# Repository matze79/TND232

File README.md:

📢 Project: TND232 – RS232 & USB SN76489 Tandy Sound Card

Home Project Site: https://www.retroianer.de

TND232 is a retro-computing hardware and software project to bring authentic Tandy/PCjr style 3-voice sound to IBM-PC compatible computers using modern interfaces like RS232 (serial) and USB, driven by the classic Texas Instruments SN76489 programmable sound generator chip.

🎯 Overview

Many classic DOS games support the Tandy 1000’s 3-voice audio produced by the SN76489 sound chip, but modern vintage add-ons like ISA boards aren’t always practical for newer PCs or laptops without expansion slots. The TND232 project provides an interface to control an SN76489 sound generator externally:

Serial (RS232) interface – connect via the PC’s COM port

USB interface – USB-powered control for systems without RS232

Drives an SN76489 sound module (3 square waves + noise) for authentic sound output on classic software

Includes DOS drivers/utilities to support music and game sound

The goal is to offer a flexible, cross-platform way to add real retro sound hardware to DOS machines without needing an ISA expansion card, while preserving authentic Tandy audio for games and demos.

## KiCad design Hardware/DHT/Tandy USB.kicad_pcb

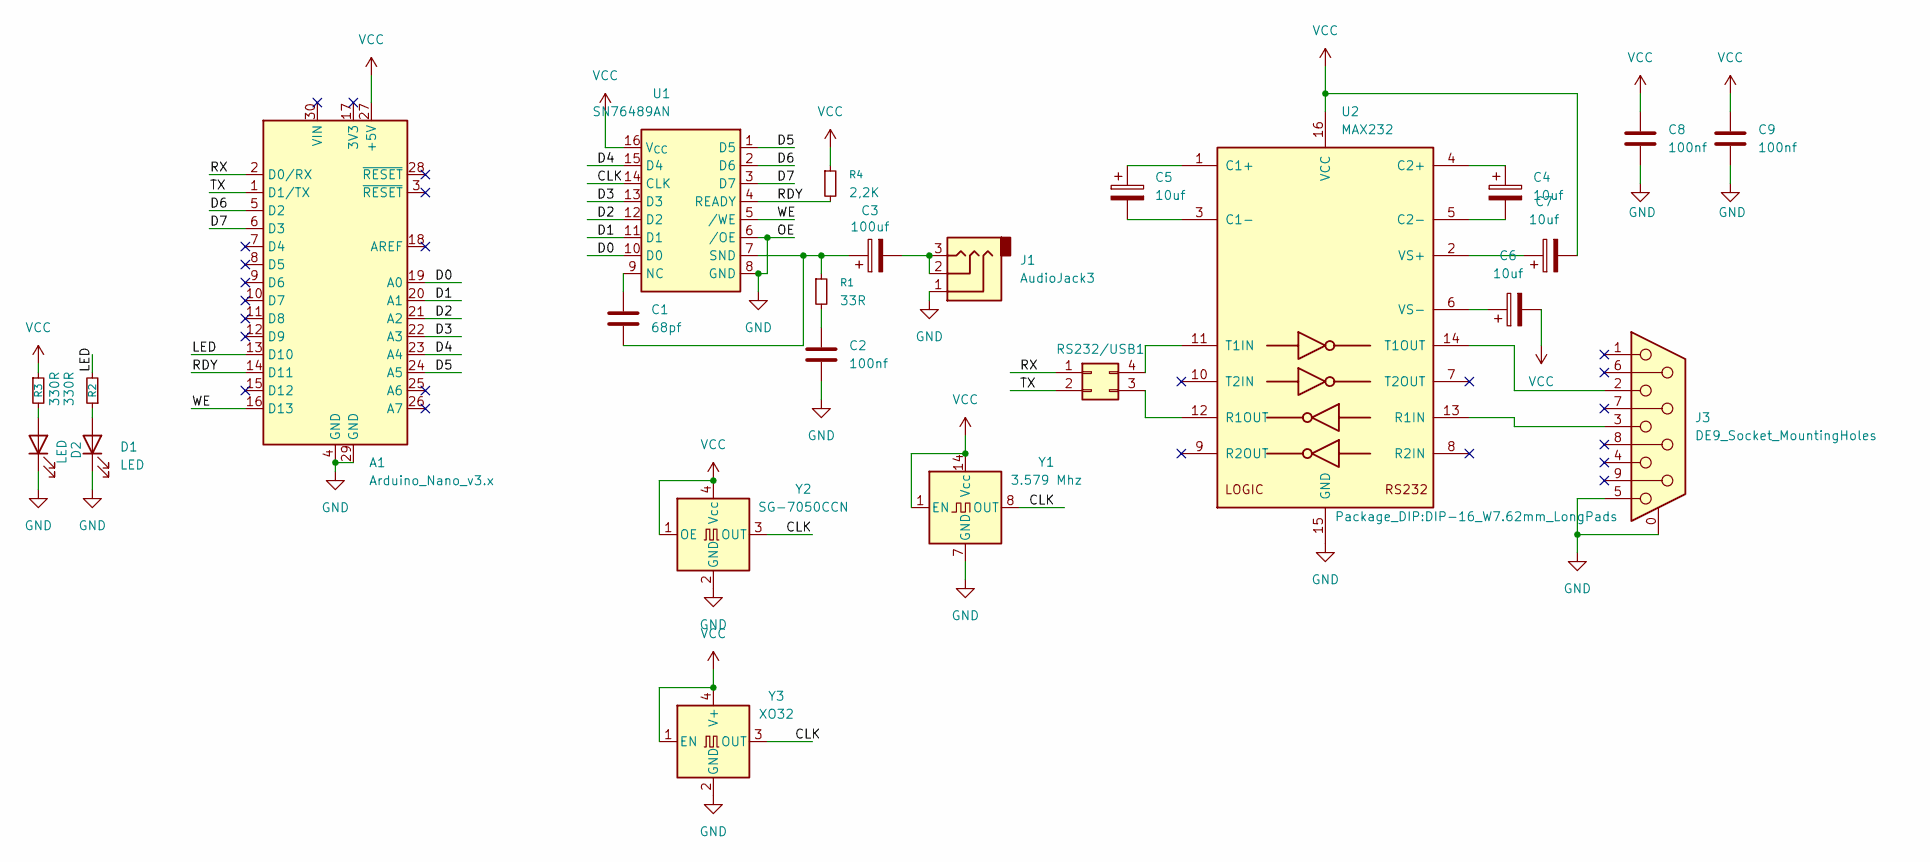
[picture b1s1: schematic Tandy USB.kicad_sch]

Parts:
A1: Arduino_Nano_v3.x; Arduino_Nano
C1: 68pf; C_Disc_D3.4mm_W2.1mm_P2.50mm
C2, C8, C9: 100nf; C_Disc_D3.4mm_W2.1mm_P2.50mm
C3: 100uf; CP_Radial_D5.0mm_P2.50mm
C4, C5, C6, C7: 10uf; CP_Radial_D5.0mm_P2.50mm
D1, D2: LED; LED_D3.0mm
J1: AudioJack3; jack_3.5_pj313d-smt
J3: DE9_Socket_MountingHoles; DSUB-9_Socket_Horizontal_P2.77x2.84mm_EdgePinOffset4.94mm_H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
R1: 33R; R_Axial_DIN0207_L6.3mm_D2.5mm_P10.16mm_Horizontal
R2, R3: 330R; R_Axial_DIN0207_L6.3mm_D2.5mm_P10.16mm_Horizontal
R4: 2,2K; R_Axial_DIN0207_L6.3mm_D2.5mm_P10.16mm_Horizontal
RS232/USB1: Conn_02x02_Counter_Clockwise; PinHeader_2x02_P2.54mm_Vertical
U1: SN76489AN; DIP-16_W7.62mm
U2: MAX232; DIP-16_W7.62mm_LongPads
Y1: 3.579 Mhz; Oscillator_DIP-14
Y2: SG-7050CCN; Oscillator_SMD_SeikoEpson_SG8002CA-4Pin_7.0x5.0mm
Y3: XO32; Oscillator_SMD_EuroQuartz_XO32-4Pin_3.2x2.5mm

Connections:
/CLK: U1.14 (CLK), Y1.8 (OUT), Y2.3 (OUT), Y3.3 (OUT)
/D0: A1.19 (A0), U1.10 (D0)
/D1: A1.20 (A1), U1.11 (D1)
/D2: A1.21 (A2), U1.12 (D2)
/D3: A1.22 (A3), U1.13 (D3)
/D4: A1.23 (A4), U1.15 (D4)
/D5: A1.24 (A5), U1.1 (D5)
/D6: A1.5 (D2), U1.2 (D6)
/D7: A1.6 (D3), U1.3 (D7)
/LED: A1.13 (D10), R2.2
/RDY: A1.14 (D11), R4.2, U1.4 (READY)
/RX: A1.2 (D0/RX), RS232/USB1.1
/TX: A1.1 (D1/TX), RS232/USB1.2
/WE: A1.16 (D13), U1.5 (/WE)
GND: A1.4 (GND), A1.29 (GND), C2.1, C8.1, C9.1, D1.1 (K), D2.1 (K), J1.1, J3.0 (PAD), J3.5, U1.6 (/OE), U1.8 (GND), U2.15 (GND), Y1.7 (GND), Y2.2 (GND), Y3.2 (GND)
unnamed: C2.2, R1.2
unnamed: C3.2, J1.2, J1.3
unnamed: D1.2 (A), R2.1
unnamed: D2.2 (A), R3.2
unnamed: RS232/USB1.3, U2.12 (R1OUT)
unnamed: RS232/USB1.4, U2.11 (T1IN)
unnamed: C1.2, U1.9 (NC)
unnamed: C1.1, C3.1, R1.1, U1.7 (SND)
unnamed: C5.1, U2.1 (C1+)
unnamed: C5.2, U2.3 (C1-)
unnamed: C4.1, U2.4 (C2+)
unnamed: C4.2, U2.5 (C2-)
unnamed: J3.3, U2.13 (R1IN)
unnamed: J3.2, U2.14 (T1OUT)
unnamed: C7.1, U2.2 (VS+)
unnamed: C6.1, U2.6 (VS-)
VCC: A1.27 (+5V), C6.2, C7.2, C8.2, C9.2, R3.1, R4.1, U1.16 (V_{CC}), U2.16 (VCC), Y1.1 (EN), Y1.14 (Vcc), Y2.1 (OE), Y2.4 (Vcc), Y3.1 (EN), Y3.4 (V+)

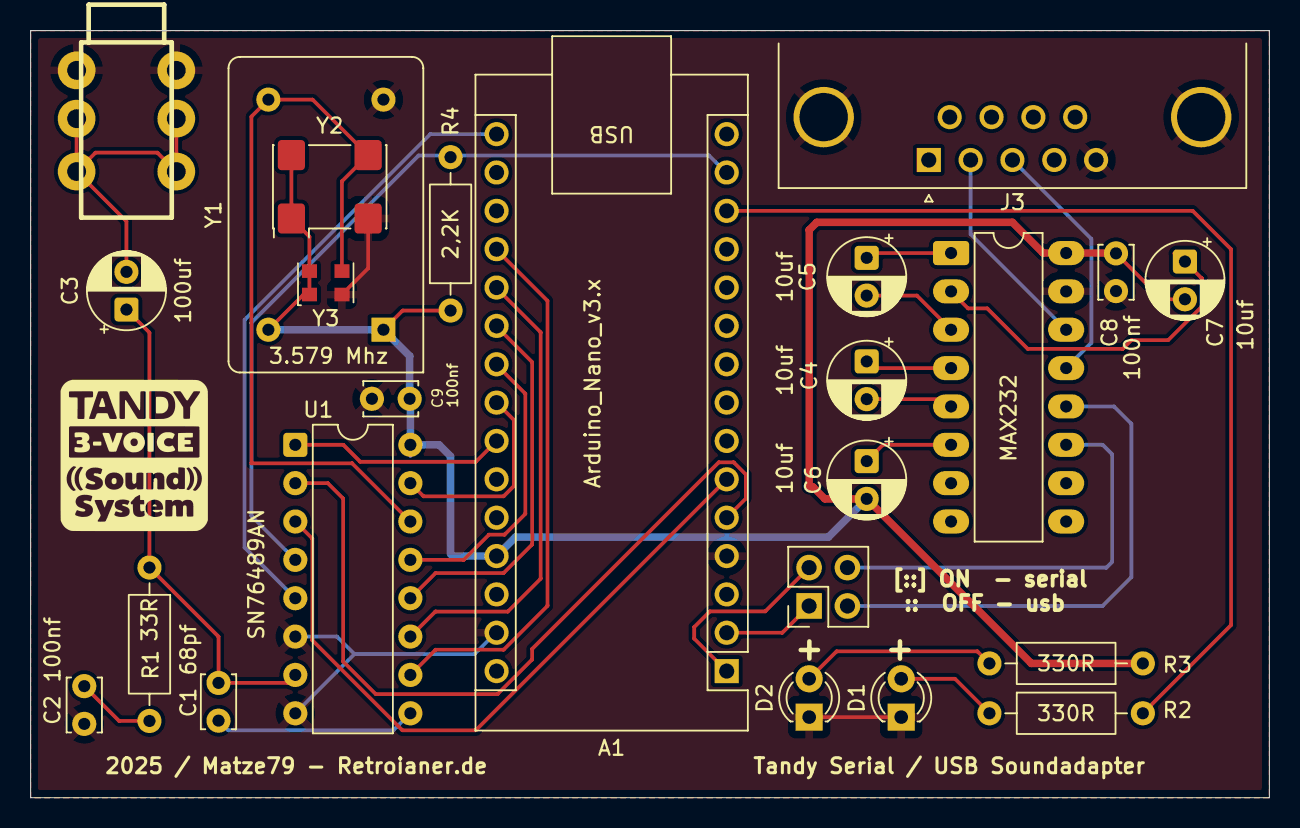
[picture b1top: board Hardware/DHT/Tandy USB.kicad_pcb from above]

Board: 2 copper layers, 82.0 x 50.8 mm, 24 parts (0 on the bottom side), 32 nets.

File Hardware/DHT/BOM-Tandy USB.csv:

Comment,Designator,Footprint,LCSC,Quantity
"2,2K",R4,R_Axial_DIN0207_L6.3mm_D2.5mm_P10.16mm_Horizontal,,1
XO32,Y3,Oscillator_SMD_EuroQuartz_XO32-4Pin_3.2x2.5mm,,1
SG-7050CCN,Y2,Oscillator_SMD_SeikoEpson_SG8002CA-4Pin_7.0x5.0mm,,1
DE9_Socket_MountingHoles,J3,DSUB-9_Socket_Horizontal_P2.77x2.84mm_EdgePinOffset4.94mm_Housed_MountingHolesOffset4.94mm,,1
LED,D1,LED_D3.0mm,,1
LED,D2,LED_D3.0mm,,1
100nf,C9,C_Disc_D3.4mm_W2.1mm_P2.50mm,,1
10uf,C6,CP_Radial_D5.0mm_P2.50mm,,1
100nf,C8,C_Disc_D3.4mm_W2.1mm_P2.50mm,,1
10uf,C7,CP_Radial_D5.0mm_P2.50mm,,1
100nf,C2,C_Disc_D3.4mm_W2.1mm_P2.50mm,,1
SN76489AN,U1,DIP-16_W7.62mm,,1
10uf,C5,CP_Radial_D5.0mm_P2.50mm,,1
3.579 Mhz,Y1,Oscillator_DIP-14,,1
10uf,C4,CP_Radial_D5.0mm_P2.50mm,,1
33R,R1,R_Axial_DIN0207_L6.3mm_D2.5mm_P10.16mm_Horizontal,,1
100uf,C3,CP_Radial_D5.0mm_P2.50mm,,1
68pf,C1,C_Disc_D3.4mm_W2.1mm_P2.50mm,,1
AudioJack3,J1,jack_3.5_pj313d-smt,,1
330R,R2,R_Axial_DIN0207_L6.3mm_D2.5mm_P10.16mm_Horizontal,,1
330R,R3,R_Axial_DIN0207_L6.3mm_D2.5mm_P10.16mm_Horizontal,,1
MAX232,U2,DIP-16_W7.62mm_LongPads,,1
Arduino_Nano_v3.x,A1,Arduino_Nano,,1

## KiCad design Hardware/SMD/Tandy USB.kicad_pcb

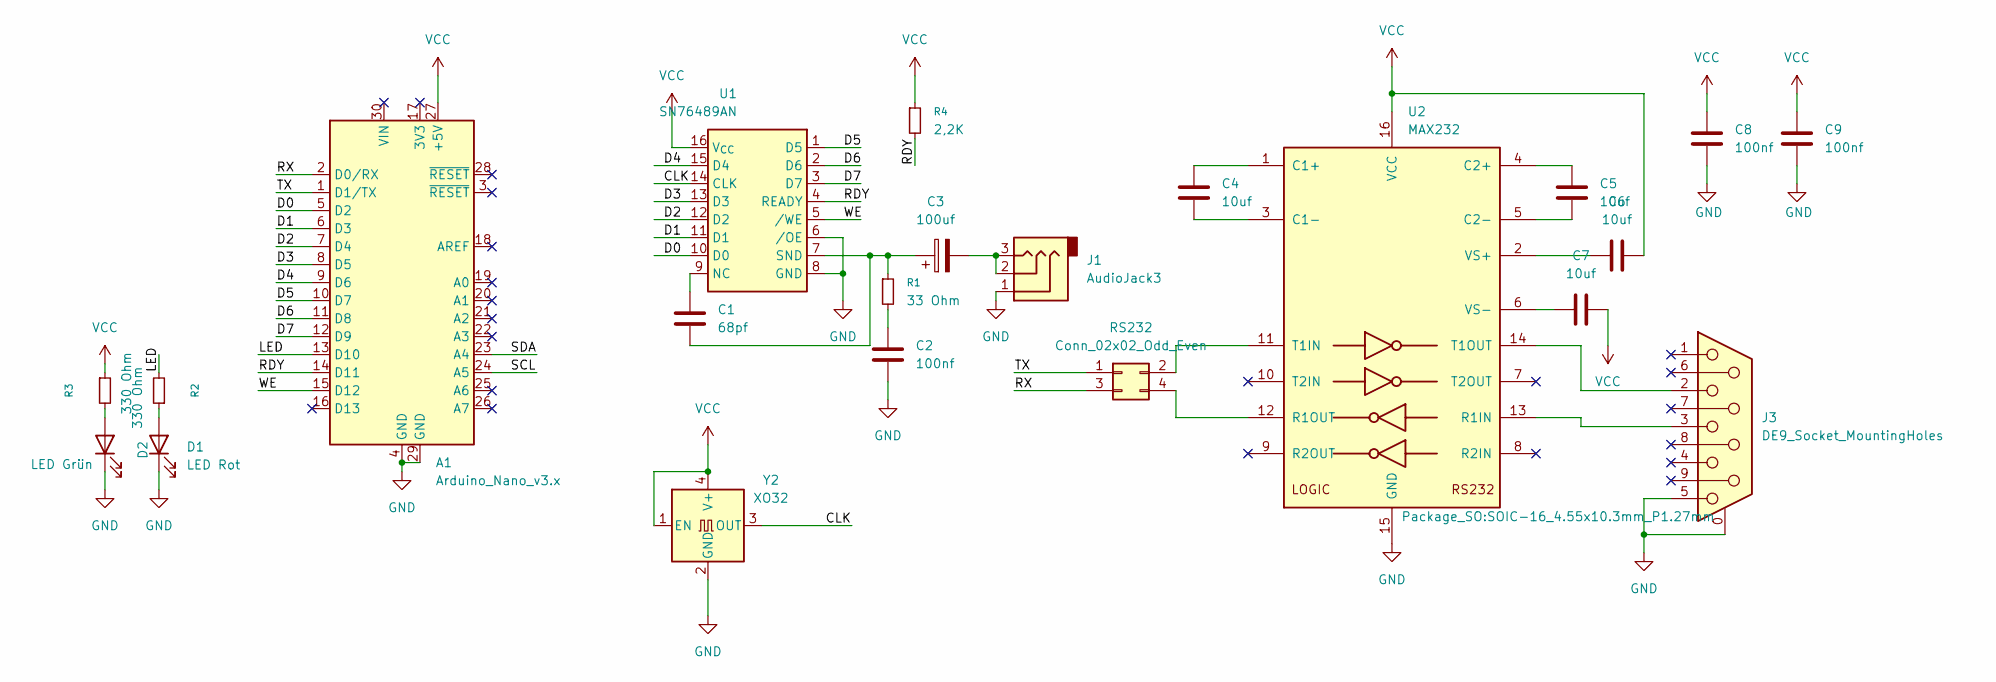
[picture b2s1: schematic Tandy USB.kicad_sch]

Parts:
A1: Arduino_Nano_v3.x; Arduino_Nano
C1: 68pf; C_0603_1608Metric_Pad1.08x0.95mm_HandSolder
C2, C8, C9: 100nf; C_0603_1608Metric_Pad1.08x0.95mm_HandSolder
C3: 100uf; CP_EIA-3216-10_Kemet-I_HandSolder
C4, C5, C6, C7: 10uf; C_0603_1608Metric_Pad1.08x0.95mm_HandSolder
D1: LED Rot; LED_0603_1608Metric_Pad1.05x0.95mm_HandSolder
D2: LED Grün; LED_0603_1608Metric_Pad1.05x0.95mm_HandSolder
J1: AudioJack3; jack_3.5_pj313d-smt
J3: DE9_Socket_MountingHoles; DSUB-9_Socket_Horizontal_P2.77x2.84mm_EdgePinOffset4.94mm_H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
R1: 33 Ohm; R_0603_1608Metric_Pad0.98x0.95mm_HandSolder
R2, R3: 330 Ohm; R_0603_1608Metric_Pad0.98x0.95mm_HandSolder
R4: 2,2K; R_0603_1608Metric_Pad0.98x0.95mm_HandSolder
RS232: Conn_02x02_Odd_Even; PinHeader_2x02_P2.54mm_Vertical
U1: SN76489AN; DIP-16_W7.62mm
U2: MAX232; SOIC-16_4.55x10.3mm_P1.27mm
Y2: XO32; Oscillator_SMD_EuroQuartz_XO32-4Pin_3.2x2.5mm

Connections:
/CLK: U1.14 (CLK), Y2.3 (OUT)
/D0: A1.5 (D2), U1.10 (D0)
/D1: A1.6 (D3), U1.11 (D1)
/D2: A1.7 (D4), U1.12 (D2)
/D3: A1.8 (D5), U1.13 (D3)
/D4: A1.9 (D6), U1.15 (D4)
/D5: A1.10 (D7), U1.1 (D5)
/D6: A1.11 (D8), U1.2 (D6)
/D7: A1.12 (D9), U1.3 (D7)
/LED: A1.13 (D10), R2.2
/RDY: A1.14 (D11), R4.2, U1.4 (READY)
/RX: A1.2 (D0/RX), RS232.3
/SCL: A1.24 (A5)
/SDA: A1.23 (A4)
/TX: A1.1 (D1/TX), RS232.1
/WE: A1.15 (D12), U1.5 (/WE)
GND: A1.4 (GND), A1.29 (GND), C2.1, C8.1, C9.1, D1.1 (K), D2.1 (K), J1.1, J3.0 (PAD), J3.5, U1.6 (/OE), U1.8 (GND), U2.15 (GND), Y2.2 (GND)
unnamed: C2.2, R1.2
unnamed: C3.2, J1.2, J1.3
unnamed: D1.2 (A), R2.1
unnamed: D2.2 (A), R3.2
unnamed: RS232.2, U2.11 (T1IN)
unnamed: RS232.4, U2.12 (R1OUT)
unnamed: C1.2, U1.9 (NC)
unnamed: C1.1, C3.1, R1.1, U1.7 (SND)
unnamed: C4.2, U2.1 (C1+)
unnamed: C4.1, U2.3 (C1-)
unnamed: C5.2, U2.4 (C2+)
unnamed: C5.1, U2.5 (C2-)
unnamed: J3.3, U2.13 (R1IN)
unnamed: J3.2, U2.14 (T1OUT)
unnamed: C6.2, U2.2 (VS+)
unnamed: C7.2, U2.6 (VS-)
VCC: A1.27 (+5V), C6.1, C7.1, C8.2, C9.2, R3.1, R4.1, U1.16 (V_{CC}), U2.16 (VCC), Y2.1 (EN), Y2.4 (V+)

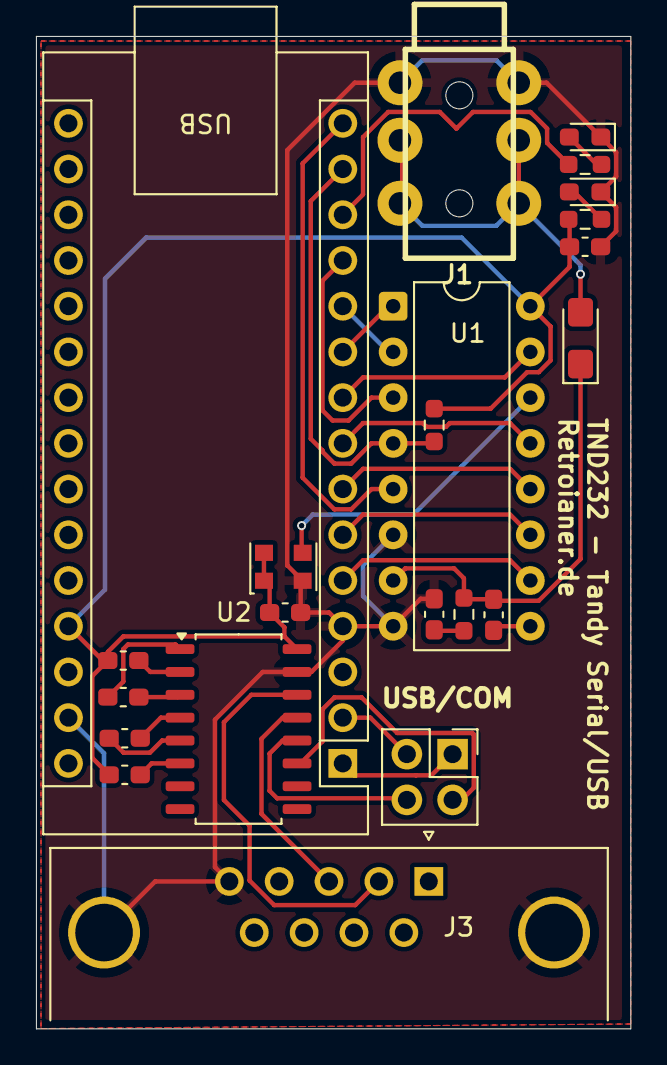
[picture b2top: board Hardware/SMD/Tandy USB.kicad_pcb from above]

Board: 2 copper layers, 33.0 x 55.1 mm, 22 parts (0 on the bottom side), 32 nets.

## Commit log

2026-01-31 TND232 Driver
    Tandy Serial Soundcard Driver
2026-01-31 Add project description for TND232 serial driver
2026-01-31 Correct Tandy SN76489 to Tandy TND232 in README
2026-02-01 PCB Files
    PCB Gerbers for Tandy DHT Variant
2026-02-01 Update README.md
    Readme updates
2026-02-01 Add project site link to README
    Added project site link to the README.
2026-02-10 Fixed upload
    Firmware
2026-02-15 PCB Files / Gerbers
    PCB Files and Gerbers added
2026-02-15 PCB Picture
    Added Picture
2026-02-15 Add image to README for TND232 project
    Added an image to the README for visual reference.
2026-02-15 Correct image link in README.md
    Fix image link in README to use correct path format.
2026-02-15 Correct image formatting in README
    Fix image syntax in README.md
2026-02-15 Update README by removing image
    Removed image from README and updated formatting.
